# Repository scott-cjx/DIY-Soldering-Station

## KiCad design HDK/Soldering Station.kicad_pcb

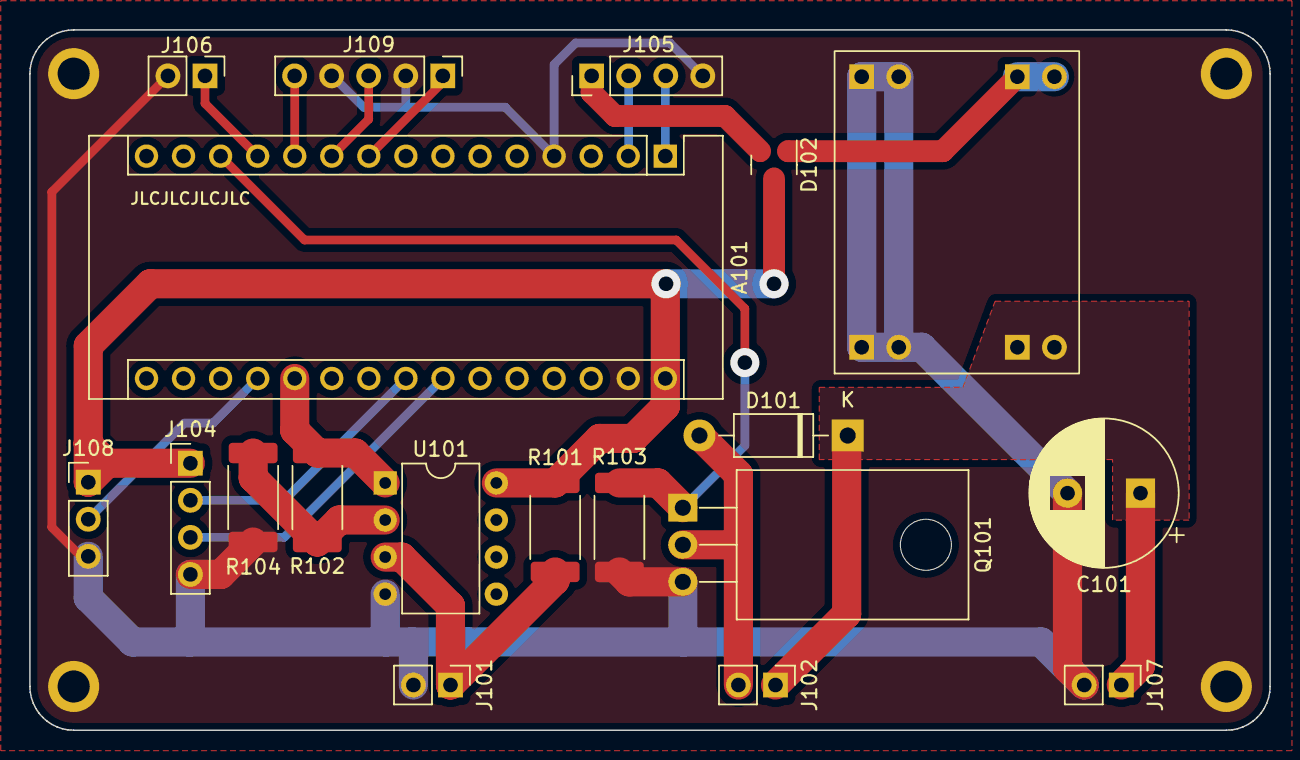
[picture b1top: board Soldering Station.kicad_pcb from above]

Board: 2 copper layers, 85.0 x 48.0 mm, 19 parts (0 on the bottom side), 19 nets.

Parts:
A101: Arduino_Nano_v3.x; Arduino_Nano
C101: 470uF; CP_Radial_D10.0mm_P5.00mm
D101: 1N4007; D_DO-41_SOD81_P10.16mm_Horizontal
D102: BAT54C; SOT-23
J101, J102, J106, J107: Conn_01x02; PinHeader_1x02_P2.54mm_Vertical
J104, J105: Conn_01x04; PinHeader_1x04_P2.54mm_Vertical
J108: Conn_01x03; PinHeader_1x03_P2.54mm_Vertical
J109: Conn_01x05; PinHeader_1x05_P2.54mm_Vertical
J110: Conn_01x04; DSUN-BUCKCONV
Q101: IRLZ44N; TO-220-3_Horizontal_TabDown
R101: 470; R_2512_6332Metric_Pad1.40x3.35mm_HandSolder
R102: 3k3; R_2512_6332Metric_Pad1.40x3.35mm_HandSolder
R103: 10k; R_2512_6332Metric_Pad1.40x3.35mm_HandSolder
R104: 2k7; R_2512_6332Metric_Pad1.40x3.35mm_HandSolder
U101: LM358; DIP-8_W7.62mm

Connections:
+5V: A101.30 (VIN), D102.3, J104.1, J108.1, R101.2, U101.8 (V+)
HEATINGELE_A: C101.1, D101.1 (K), J102.1, J107.1, J110.2
HEATINGELE_B: D101.2 (A), J102.2, Q101.2 (D)
I2C_SCL: A101.24 (A5), J104.3
I2C_SDA: A101.23 (A4), J104.2
MCU_ENC_A: A101.9 (D6), J109.1
MCU_ENC_B: A101.10 (D7), J109.3
MCU_ENC_BTN: A101.11 (D8), J109.5
MCU_HEATINGELE: A101.13 (D10), Q101.1 (G), R103.2
MCU_OVERRIDE: A101.12 (D9), J106.1
MCU_POT: A101.19 (A0), J108.2
MCU_TSENSOR: A101.20 (A1), R102.2, U101.1
unnamed: R102.1, R104.2, U101.2 (-)
SENSOR_A: J101.1, R101.1, U101.3 (+)
SENSOR_B: A101.4 (GND), A101.29 (GND), C101.2, J101.2, J104.4, J105.4, J106.2, J107.2, J108.3, J109.2, J109.4, J110.1, J110.3, Q101.3 (S), R103.1, R104.1, U101.4 (V-)
UART_RX: A101.2 (D0/RX), J105.2
UART_TX: A101.1 (D1/TX), J105.3
VCC_5V_IN1: D102.1, J110.4
VCC_5V_IN2: D102.2, J105.1

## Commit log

2022-10-02 init commit HDK
